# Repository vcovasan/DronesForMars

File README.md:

# DronesForMars

The repository includes the following:

1. Step files of the autopilot PCB, pinout diagrams and gerber files
2. XFLR5 models of the bare airframe and the elevon-augmented airframe for various deflection angles
3. Simscape models of the servo and BLDC motors used for Hardware-in-the-Loop testing
4. Simulink files for data collection and conditioning for actuator feedback and sensor data
5. Simulink implementation of the LQG autopilot 
6. Arduino implementation of the autopilot, automatically generated with Matlab Embedded Coder

And many diagrams explaining the overall architecture, system requirements, specifications and test cases.

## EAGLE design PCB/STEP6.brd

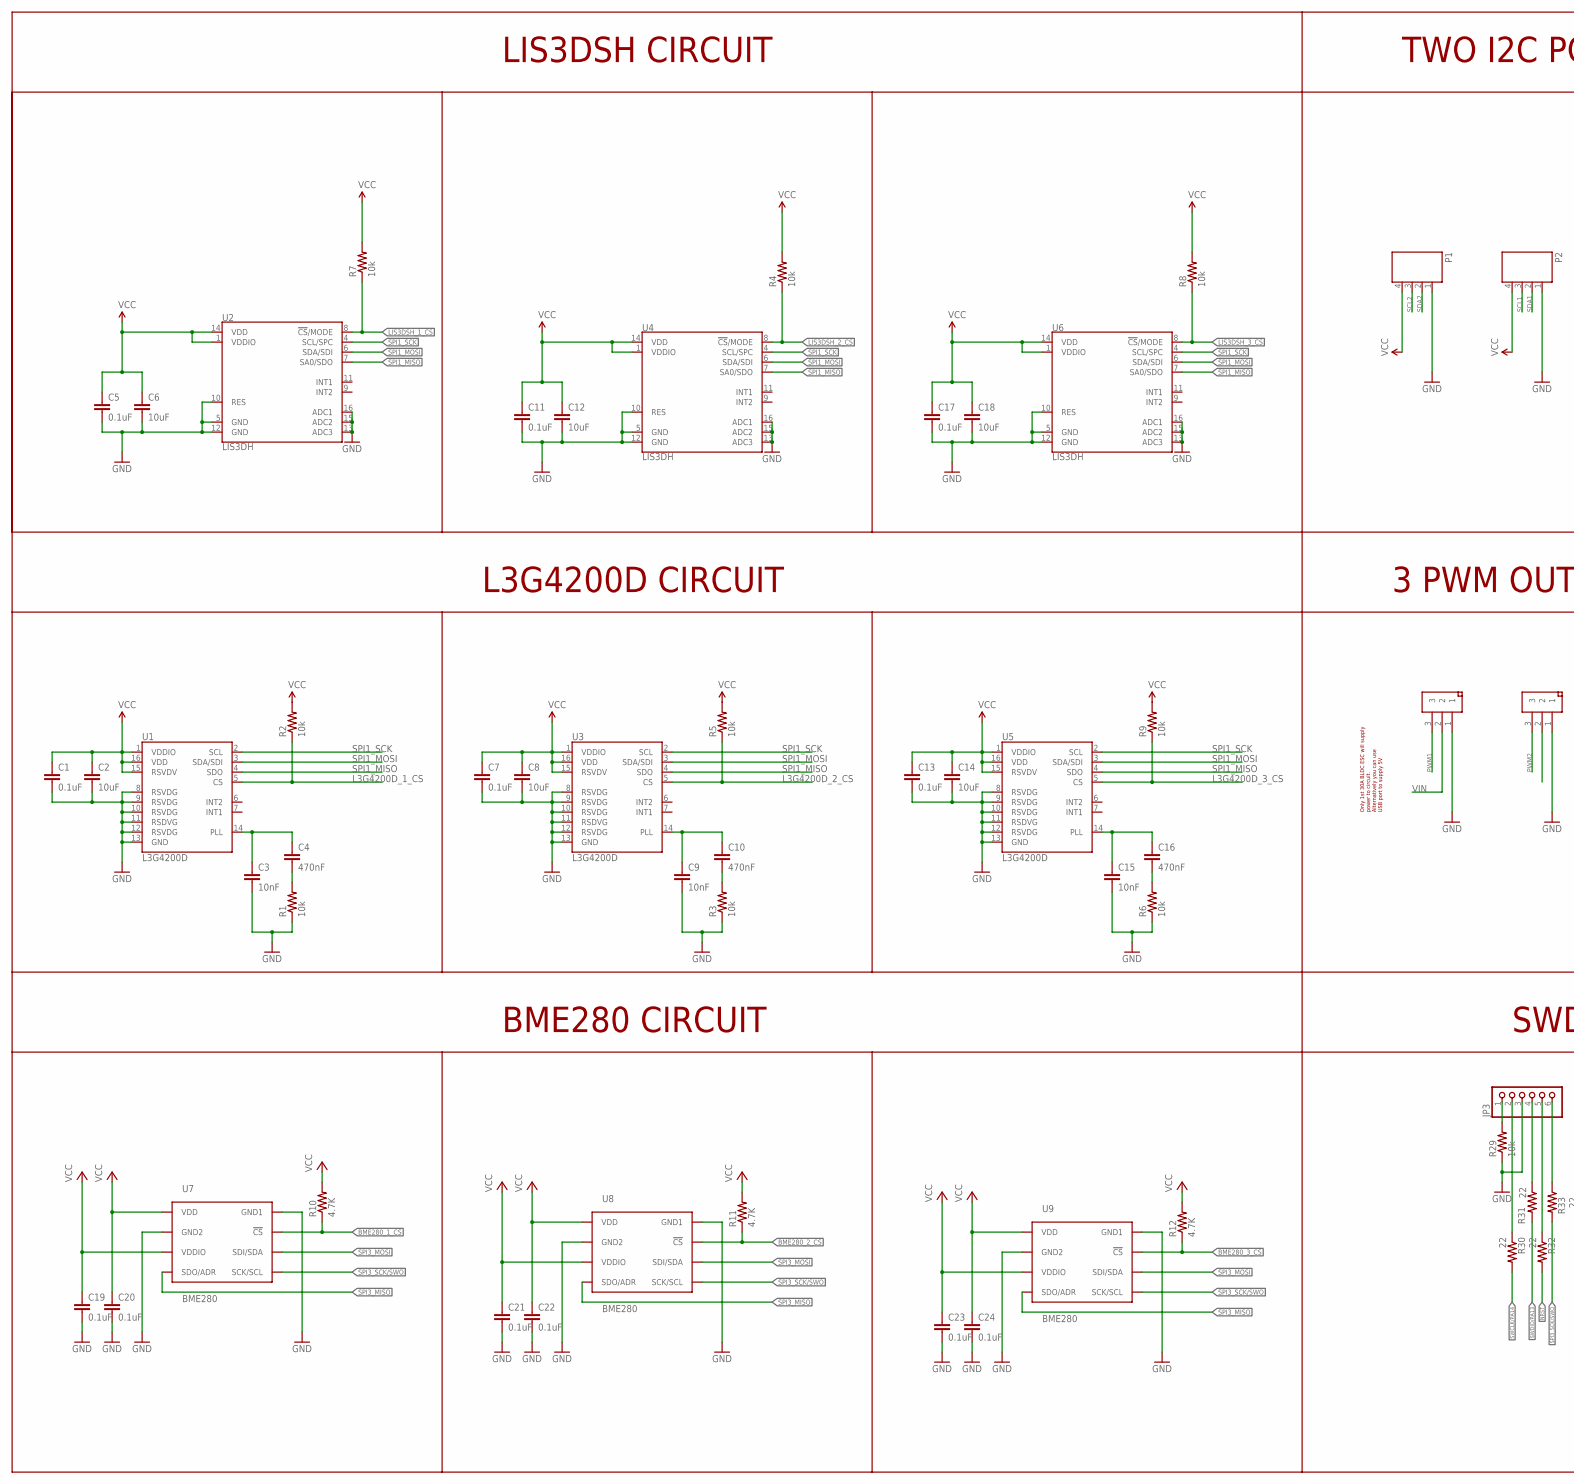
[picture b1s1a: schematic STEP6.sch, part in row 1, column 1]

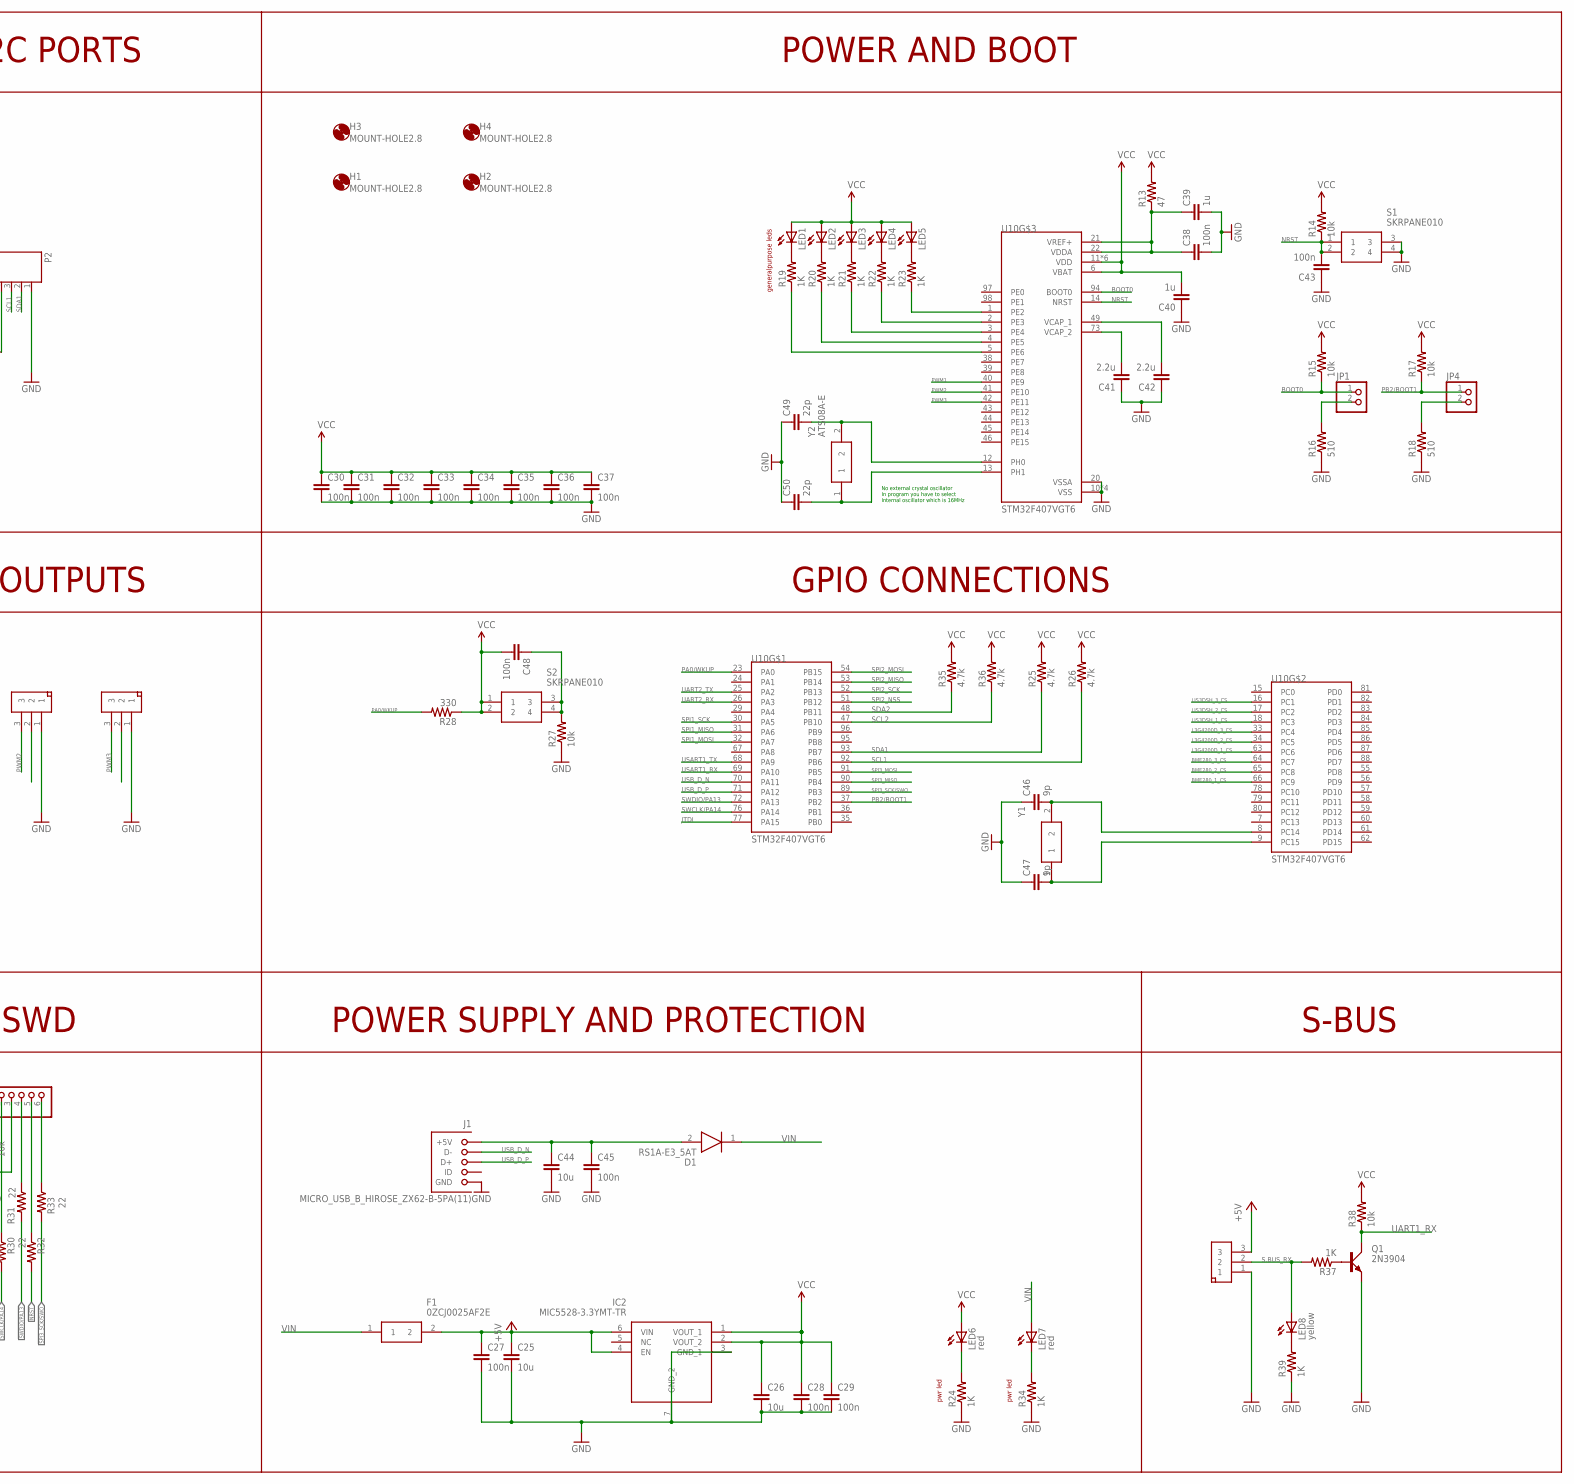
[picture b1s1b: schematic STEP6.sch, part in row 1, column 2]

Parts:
C1, C7, C13: 0.1uF; 0402-CAP
C2, C8, C14: 10uF; 1206
C3, C9, C15: 10nF; 0402-CAP
C4, C10, C16: 470nF; 0402-CAP
C5, C11, C17: 0.1uF; 0402
C6, C12, C18: 10uF; 0603
C19, C20, C21, C22, C23, C24: 0.1uF; 0603-CAP
C25, C26, C44: 10u; C0805
C27, C28, C29, C30, C31, C32, C33, C34, C35, C36, C37, C38, C43, C45, C48: 100n; C0402
C39, C40: 1u; C0402
C41, C42: 2.2u; C0603
C46, C47: 9p; C0402
C49, C50: 22p; C0402
D1: RS1A-E3_5AT; DIOM5127X229N
F1: 0ZCJ0025AF2E; FUSC3216X75N
H1, H2, H3, H4: MOUNT-HOLE2.8; 2,8
IC2: MIC5528-3.3YMT-TR; SON40P120X120X60-7N
J1: MICRO_USB_B_HIROSE_ZX62-B-5PA(11); USB_MICRO_B-HIROSE-ZX62-B-5PA(11)
JP1, JP4: PINHD-1X2; 1X02
JP3: PINHD-1X6; 1X06
LED1, LED2, LED3, LED4, LED5: LEDCHIP-LED0603; CHIP-LED0603
LED6, LED7: red; CHIP-LED0603
LED8: yellow; CHIP-LED0603
P1, P2: JST-PH4
Q1: 2N3904; SOT23
R1, R2, R3, R5, R6, R9, R29: 10k; 0402-RES
R4, R7, R8, R14, R15, R17, R27, R38: 10k; R0402
R10, R11, R12: 4.7K; R0402
R13: 47; R1206
R16, R18: 510; R0402
R19, R20, R21, R22, R23, R24, R34, R37, R39: 1K; R0402
R25, R26, R35, R36: 4.7k; R0402
R28: 330; R0402
R30, R31, R32, R33: 22; 0402-RES
S1, S2: SKRPANE010; SKRPADE010
U1, U3, U5: L3G4200D; LGA16-4X4
U2, U4, U6: LIS3DH; LGA-16-3X3
U7, U8, U9: BME280; BME280_LGA
U10: STM32F407VGT6; QFP50P1600X1600X160-100N
U$1, U$2, U$3, U$4: JST-PH3
Y1: CM7V-T1A-32.768K-9PF-20PPM-TA-; CM7VT1A32768KHZ125PF10PPMTBQC
Y2: ATS08A-E; ATS041C-E

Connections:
+5V: C25.1, C27.1, F1.2, IC2.4 (EN), IC2.6 (VIN), U$4.3
BME280_1_CS: R10.1, U7.P$2 (!CS), U10.66 (PC9)
BME280_2_CS: R11.1, U8.P$2 (!CS), U10.65 (PC8)
BME280_3_CS: R12.1, U9.P$2 (!CS), U10.64 (PC7)
BOOT0: JP1.1, R15.1, U10.94 (BOOT0)
GND: C1.2, C2.2, C3.2, C5.2, C6.2, C7.2, C8.2, C9.2, C11.2, C12.2, C13.2, C14.2, C15.2, C17.2, C18.2, C19.2, C20.2, C21.2, C22.2, C23.2, C24.2, C25.2, C26.2, C27.2, C28.2, C29.2, C30.2, C31.2, C32.2, C33.2, C34.2, C35.2, C36.2, C37.2, C38.2, C39.2, C40.1, C41.1, C42.1, C43.1, C44.2, C45.2, C46.1, C47.1, C49.1, C50.1, IC2.3 (GND_1), IC2.7 (GND_2), J1.5 (GND), JP3.3, P1.1, P2.1, Q1.2 (E), R1.1, R3.1, R6.1, R16.1, R18.1, R24.1, R27.1, R29.1, R34.1, R39.1, S1.3, S1.4, U1.8 (RSVDG), U1.9 (RSVDG), U1.10 (RSVDG), U1.11 (RSDVG), U1.12 (RSVDG), U1.13 (GND), U2.5 (GND), U2.10 (RES), U2.12 (GND), U2.13 (ADC3), U2.15 (ADC2), U2.16 (ADC1), U3.8 (RSVDG), U3.9 (RSVDG), U3.10 (RSVDG), U3.11 (RSDVG), U3.12 (RSVDG), U3.13 (GND), U4.5 (GND), U4.10 (RES), U4.12 (GND), U4.13 (ADC3), U4.15 (ADC2), U4.16 (ADC1), U5.8 (RSVDG), U5.9 (RSVDG), U5.10 (RSVDG), U5.11 (RSDVG), U5.12 (RSVDG), U5.13 (GND), U6.5 (GND), U6.10 (RES), U6.12 (GND), U6.13 (ADC3), U6.15 (ADC2), U6.16 (ADC1), U7.P$1 (GND1), U7.P$7 (GND2), U8.P$1 (GND1), U8.P$7 (GND2), U9.P$1 (GND1), U9.P$7 (GND2), U10.10 (VSS), U10.20 (VSSA), U10.27 (VSS), U10.74 (VSS), U10.99 (VSS), U$1.1, U$2.1, U$3.1, U$4.1
JTDI: U10.77 (PA15)
L3G4200D_1_CS: R2.1, U1.5 (CS), U10.63 (PC6)
L3G4200D_2_CS: R5.1, U3.5 (CS), U10.34 (PC5)
L3G4200D_3_CS: R9.1, U5.5 (CS), U10.33 (PC4)
LIS3DSH_1_CS: R7.1, U2.8 (!CS!/MODE), U10.18 (PC3)
LIS3DSH_2_CS: R4.1, U4.8 (!CS!/MODE), U10.17 (PC2)
LIS3DSH_3_CS: R8.1, U6.8 (!CS!/MODE), U10.16 (PC1)
unnamed: C42.2, U10.49 (VCAP_1)
unnamed: C38.1, C39.1, R13.1, U10.21 (VREF+), U10.22 (VDDA)
unnamed: C41.2, U10.73 (VCAP_2)
unnamed: JP1.2, R16.2
unnamed: LED1.C, R19.2
unnamed: JP4.2, R18.2
unnamed: LED2.C, R20.2
unnamed: LED3.C, R21.2
unnamed: LED4.C, R22.2
unnamed: LED5.C, R23.2
unnamed: R23.1, U10.1 (PE2)
unnamed: LED6.C, R24.2
unnamed: R22.1, U10.2 (PE3)
unnamed: R21.1, U10.3 (PE4)
unnamed: R20.1, U10.4 (PE5)
unnamed: R19.1, U10.5 (PE6)
unnamed: C46.2, U10.8 (PC14), Y1.2
unnamed: C47.2, U10.9 (PC15), Y1.1
unnamed: C48.1, R27.2, S2.3, S2.4
unnamed: JP3.1, R29.2
unnamed: JP3.2, R30.1
unnamed: JP3.4, R31.1
unnamed: JP3.5, R32.1
unnamed: JP3.6, R33.1
unnamed: C49.2, U10.12 (PH0), Y2.2
unnamed: C50.2, U10.13 (PH1), Y2.1
unnamed: LED7.C, R34.2
unnamed: Q1.1 (B), R37.1
unnamed: LED8.C, R39.2
NRST: C43.2, R14.1, R32.2, S1.1, S1.2, U10.14 (NRST)
PA0/WKUP: R28.2, U10.23 (PA0)
PB2/BOOT1: JP4.1, R17.1, U10.37 (PB2)
PLL: C3.1, C4.1, U1.14 (PLL)
PLL1: C9.1, C10.1, U3.14 (PLL)
PLL2: C15.1, C16.1, U5.14 (PLL)
PLL-1: C10.2, R3.2
PLL-2: C4.2, R1.2
PLL-3: C16.2, R6.2
PWM1: U10.40 (PE9), U$1.3
PWM2: U10.41 (PE10), U$2.3
PWM3: U10.42 (PE11), U$3.3
S.BUS_RX: LED8.A, R37.2, U$4.2
SCL1: P2.3, R26.1, U10.92 (PB6)
SCL2: P1.3, R36.1, U10.47 (PB10)
SDA1: P2.2, R25.1, U10.93 (PB7)
SDA2: P1.2, R35.1, U10.48 (PB11)
SPI1_MISO: U1.4 (SDO), U2.7 (SA0/SDO), U3.4 (SDO), U4.7 (SA0/SDO), U5.4 (SDO), U6.7 (SA0/SDO), U10.31 (PA6)
SPI1_MOSI: U1.3 (SDA/SDI), U2.6 (SDA/SDI), U3.3 (SDA/SDI), U4.6 (SDA/SDI), U5.3 (SDA/SDI), U6.6 (SDA/SDI), U10.32 (PA7)
SPI1_SCK: U1.2 (SCL), U2.4 (SCL/SPC), U3.2 (SCL), U4.4 (SCL/SPC), U5.2 (SCL), U6.4 (SCL/SPC), U10.30 (PA5)
SPI2_MISO: U10.53 (PB14)
SPI2_MOSI: U10.54 (PB15)
SPI2_NSS: U10.51 (PB12)
SPI2_SCK: U10.52 (PB13)
SPI3_MISO: U7.P$5 (SDO/ADR), U8.P$5 (SDO/ADR), U9.P$5 (SDO/ADR), U10.90 (PB4)
SPI3_MOSI: U7.P$3 (SDI/SDA), U8.P$3 (SDI/SDA), U9.P$3 (SDI/SDA), U10.91 (PB5)
SPI3_SCK/SWO: R33.2, U7.P$4 (SCK/SCL), U8.P$4 (SCK/SCL), U9.P$4 (SCK/SCL), U10.89 (PB3)
SWCLK/PA14: R30.2, U10.76 (PA14)
SWDIO/PA13: R31.2, U10.72 (PA13)
UART1_RX: Q1.3 (C), R38.1
UART2_RX: U10.26 (PA3)
UART2_TX: U10.25 (PA2)
USART1_RX: U10.69 (PA10)
USART1_TX: U10.68 (PA9)
USB_D_N: J1.2 (D-), U10.70 (PA11)
USB_D_P: J1.3 (D+), U10.71 (PA12)
VCC: C1.1, C2.1, C5.1, C6.1, C7.1, C8.1, C11.1, C12.1, C13.1, C14.1, C17.1, C18.1, C19.1, C20.1, C21.1, C22.1, C23.1, C24.1, C26.1, C28.1, C29.1, C30.1, C31.1, C32.1, C33.1, C34.1, C35.1, C36.1, C37.1, C40.2, C48.2, IC2.1 (VOUT_1), IC2.2 (VOUT_2), LED1.A, LED2.A, LED3.A, LED4.A, LED5.A, LED6.A, P1.4, P2.4, R2.2, R4.2, R5.2, R7.2, R8.2, R9.2, R10.2, R11.2, R12.2, R13.2, R14.2, R15.2, R17.2, R25.2, R26.2, R28.1, R35.2, R36.2, R38.2, S2.1, S2.2, U1.1 (VDDIO), U1.15 (RSVDV), U1.16 (VDD), U2.1 (VDDIO), U2.14 (VDD), U3.1 (VDDIO), U3.15 (RSVDV), U3.16 (VDD), U4.1 (VDDIO), U4.14 (VDD), U5.1 (VDDIO), U5.15 (RSVDV), U5.16 (VDD), U6.1 (VDDIO), U6.14 (VDD), U7.P$6 (VDDIO), U7.P$8 (VDD), U8.P$6 (VDDIO), U8.P$8 (VDD), U9.P$6 (VDDIO), U9.P$8 (VDD), U10.6 (VBAT), U10.11 (VDD), U10.19 (VDD), U10.28 (VDD), U10.50 (VDD), U10.75 (VDD), U10.100 (VDD)
VIN: D1.1 (K), F1.1, LED7.A, U$1.2
VUSB: C44.1, C45.1, D1.2 (A), J1.1 (+5V)

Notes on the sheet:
LIS3DSH CIRCUIT
L3G4200D CIRCUIT
BME280 CIRCUIT
TWO I2C PORTS
POWER AND BOOT
generalpurpose leds
pwr led
3 PWM OUTPUTS
No external crystal oscillator In program you have to select Internal oscillator which is 16MHz
SWD
Only 1st 30A BLDC ESC will supply power to circuit. Alternatively you can use USB port to supply 5V
GPIO CONNECTIONS
POWER SUPPLY AND PROTECTION
S-BUS

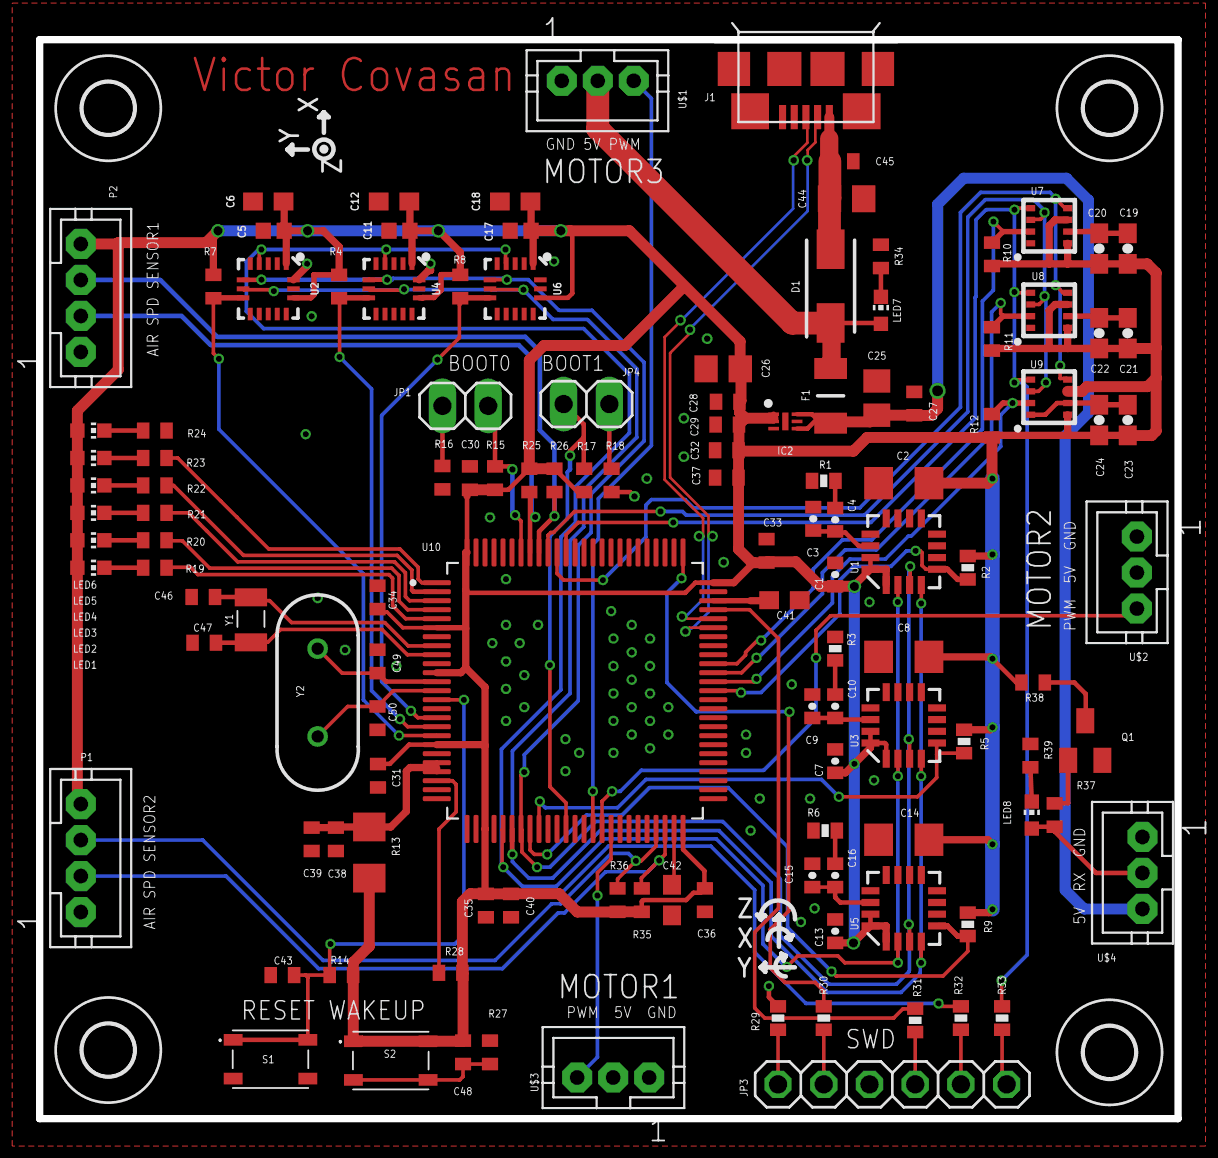
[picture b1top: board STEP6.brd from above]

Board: 2 copper layers, 63.2 x 59.9 mm, 129 parts (0 on the bottom side), 72 nets.

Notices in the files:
parts and their libraries:
SparkFun-Sensors: Licensing: Creative Commons ShareAlike 4.0 International - https://creativecommons.org/licenses/by-sa/4.0
